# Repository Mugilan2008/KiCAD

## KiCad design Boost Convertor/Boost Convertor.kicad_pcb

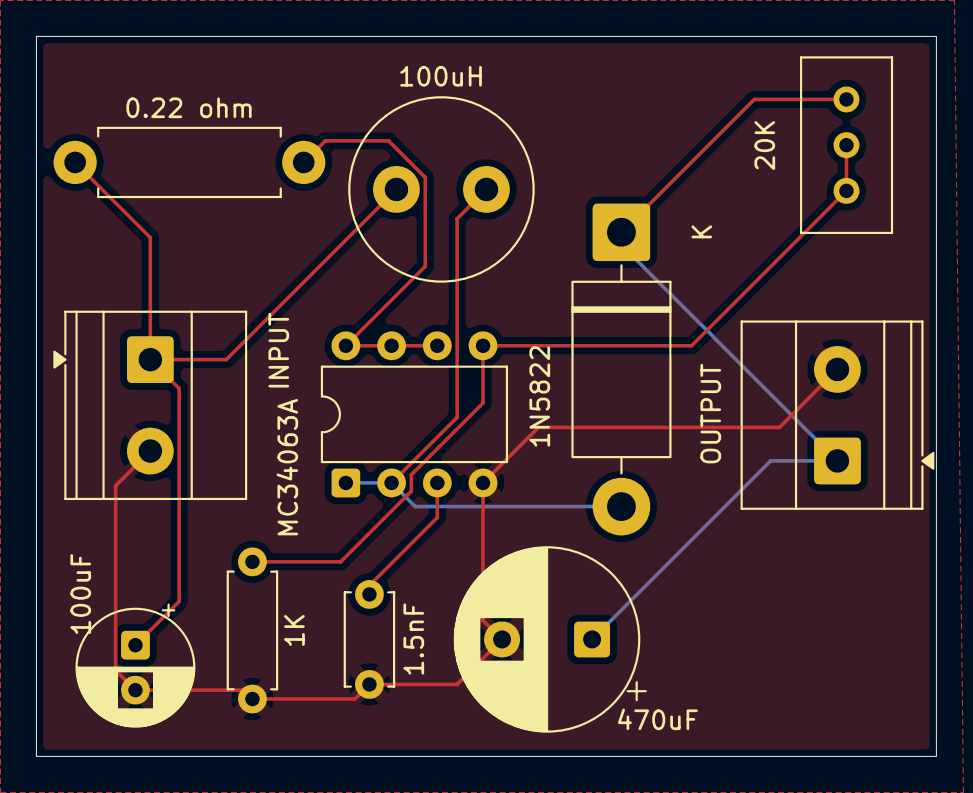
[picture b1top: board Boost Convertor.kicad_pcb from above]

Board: 2 copper layers, 50.0 x 40.0 mm, 11 parts (0 on the bottom side), 7 nets.

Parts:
0.22 ohm: 0.22; R_Axial_DIN0411_L9.9mm_D3.6mm_P12.70mm_Horizontal
1.5nF: 1.5nF; C_Disc_D5.0mm_W2.5mm_P5.00mm
1K: 1K; R_Axial_DIN0207_L6.3mm_D2.5mm_P7.62mm_Horizontal
1N5822: 1N5822; D_DO-201AD_P15.24mm_Horizontal
20K: 20k; Potentiometer_Bourns_3296W_Vertical
100uF: 100uF; CP_Radial_D6.3mm_P2.50mm
100uH: 100uH; L_Radial_D10.0mm_P5.00mm_Fastron_07M
470uF: 470uF; CP_Radial_D10.0mm_P5.00mm
INPUT: Screw_Terminal_01x02; TerminalBlock_Phoenix_MKDS-1,5-2-5.08_1x02_P5.08mm_Horizont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
MC34063A: MC34063AP; DIP-8_W7.62mm
OUTPUT: Screw_Terminal_01x02; TerminalBlock_Phoenix_MKDS-1,5-2-5.08_1x02_P5.08mm_Horizont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

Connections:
GND: 1.5nF.2, 1K.2, 100uF.2, 470uF.2, INPUT.2, MC34063A.4 (GND), OUTPUT.2
unnamed: 1N5822.2 (A), 100uH.2, MC34063A.1 (SwC), MC34063A.2 (SwE)
unnamed: 1N5822.1 (K), 20K.1, 470uF.1, OUTPUT.1
unnamed: 0.22 ohm.1, 100uF.1, 100uH.1, INPUT.1
unnamed: 0.22 ohm.2, MC34063A.6 (Vin), MC34063A.7 (Ipk), MC34063A.8 (DC)
unnamed: 1.5nF.1, MC34063A.3 (TC)
unnamed: 1K.1, 20K.2, 20K.3, MC34063A.5 (Vfb)
